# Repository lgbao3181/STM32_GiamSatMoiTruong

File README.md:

# Dự án STM32F103C8T6 – Giám sát nhiệt độ, độ ẩm và rò rỉ khí gas

## Giới thiệu

Đây là một dự án **Embedded Systems** sử dụng **STM32F103C8T6** làm vi điều khiển trung tâm để xây dựng hệ thống **giám sát nhiệt độ, độ ẩm và phát hiện rò rỉ khí gas**.

Firmware được phát triển bằng cách kết hợp **STM32CubeMX** để cấu hình phần cứng, ngoại vi và mã khởi tạo với **PlatformIO** để quản lý project, biên dịch và nạp firmware.

Hệ thống sử dụng:

* **AHT20** giao tiếp **I2C** để đo nhiệt độ và độ ẩm.
* **MQ-2** để phát hiện khí gas/khói và đưa tín hiệu cảnh báo về STM32.
* **LCD 16x2 giao tiếp I2C** để hiển thị nhiệt độ, độ ẩm và trạng thái cảnh báo.
* **Mạch chuyển mức logic 5V ↔ 3.3V** để bảo đảm tương thích mức điện áp giữa các thiết bị ngoại vi và STM32F103C8T6, đặc biệt trên các tín hiệu giao tiếp với LCD I2C và MQ-2.
* **Relay 5V** để điều khiển đèn cảnh báo **220V**.
* **UART** để truyền dữ liệu đo được từ STM32 lên PC.
* **Ứng dụng C# WinForms tự xây dựng** trên PC để hiển thị nhiệt độ, độ ẩm, trạng thái rò rỉ khí gas và đưa ra cảnh báo khi giá trị vượt ngưỡng cài đặt.

Mục tiêu của dự án là xây dựng một hệ thống giám sát thực tế, đồng thời thực hành các kỹ năng **STM32, I2C, GPIO, UART, điều khiển relay, xử lý ngưỡng cảnh báo và giao tiếp giữa MCU với phần mềm PC**.

---

## Video minh họa

https://github.com/user-attachments/assets/8e566ba1-eada-4bce-8f40-15832d237c19

---

## Sơ đồ nguyên lý

Sơ đồ nguyên lý thể hiện các khối chức năng chính của hệ thống:

* **STM32F103C8T6**: MCU trung tâm, thực hiện đọc cảm biến, xử lý điều kiện cảnh báo, điều khiển LCD, relay và truyền dữ liệu UART.
* **AHT20**: cảm biến nhiệt độ và độ ẩm, giao tiếp với STM32 thông qua I2C.
* **LCD 16x2 + module I2C**: hiển thị thông tin đo được và trạng thái cảnh báo.
* **MQ-2**: cảm biến dùng để phát hiện khí gas/khói; tín hiệu từ module được đưa qua mạch chuyển mức phù hợp trước khi vào MCU.
* **Mạch chuyển mức 5V ↔ 3.3V**: bảo đảm tương thích mức logic giữa STM32F103C8T6 và các ngoại vi sử dụng mức điện áp khác nhau, đặc biệt trên tuyến I2C của LCD và tín hiệu từ module MQ-2.
* **Relay 5V**: nhận tín hiệu điều khiển từ MCU để đóng/cắt đèn cảnh báo 220V.
* **USB–UART / UART**: cầu nối truyền dữ liệu giữa STM32 và PC.

## Thành phần phần cứng

| Thành phần | Số lượng | Vai trò |
| ------------------------------ | -------: | ----------------------------------------------- |
| STM32F103C8T6 | 1 | MCU trung tâm, xử lý dữ liệu và điều khiển hệ thống |
| AHT20 | 1 | Đo nhiệt độ và độ ẩm qua I2C |
| LCD 16x2 + module I2C | 1 | Hiển thị nhiệt độ, độ ẩm và cảnh báo |
| MQ-2 | 1 | Phát hiện khí gas/khói bằng ngõ ra số DO |
| Mạch chuyển mức 5V ↔ 3.3V | 1 | Tương thích mức logic giữa ngoại vi và STM32 |
| Relay 5V | 1 | Đóng/cắt tải cảnh báo |
| Đèn/tải 220V | 1 | Cảnh báo bằng tín hiệu đèn |
| USB–UART Converter | 1 | Cầu nối UART giữa STM32 và PC |
| PC / Laptop | 1 | Chạy ứng dụng WinForms để giám sát |

---

## Cấu hình giao tiếp và chân

> Một số chân GPIO phụ thuộc trực tiếp vào file cấu hình STM32CubeMX và project PlatformIO. Bảng dưới đây mô tả **chức năng giao tiếp**, còn số chân cụ thể nên lấy theo schematic/.ioc của phiên bản project đang sử dụng.

### AHT20 – STM32F103C8T6 (I2C)

| STM32 | Chức năng | AHT20 | Ghi chú |
| -------------------------------- | ------- | ----- | ------------------------------------------------ |
| **GPIO PB10** | I2C2 SCL | SCL | Đường xung clock của AHT20 |
| **GPIO PB11** | I2C2 SDA | SDA | Đường dữ liệu của AHT20 |
| 3.3V | Nguồn | VCC | Cấp nguồn theo thiết kế |
| GND | Mass | GND | **Bắt buộc nối chung** |

### LCD 16x2 – Module I2C – STM32

| STM32 / Bus | Chức năng | LCD I2C | Ghi chú |
| ---------------- | --------- | ------- | ------------------------------------------ |
| **GPIO PB6** | I2C1 SCL | SCL | Đường clock LCD, đi qua mạch chuyển mức |
| **GPIO PB7** | I2C1 SDA | SDA | Đường dữ liệu LCD, đi qua mạch chuyển mức |
| GND | Mass | GND | **Bắt buộc nối chung ở phía logic** |
| 5V | Nguồn LCD | VCC | Theo thiết kế phần cứng của module LCD |

### MQ-2 – STM32F103C8T6

| Tín hiệu | Chức năng | Kết nối MCU | Ghi chú |
| -------- | --------- | ----------- | ---------------------------------------------- |
| **DO** | Digital Output | **GPIO PA3** | Tín hiệu phải đi qua mạch chuyển mức 5V -> 3.3V trước khi vào MCU |
| VCC | Nguồn | 5V | Theo module MQ-2 |
| GND | Mass | GND | Nối chung với hệ thống |

> Trong project này, cảm biến MQ-2 được sử dụng thông qua ngõ ra số DO, không sử dụng ADC để đo hoặc tính toán nồng độ khí gas. Module MQ-2 được cấp nguồn 5V, do đó tín hiệu DO cần được đưa qua mạch chuyển mức logic/giảm áp trước khi kết nối với GPIO 3.3V của STM32F103C8T6.

> Về trạng thái tín hiệu, DO = 1 khi chưa phát hiện khí gas vượt ngưỡng cài đặt và DO = 0 khi phát hiện nồng độ khí vượt ngưỡng. Ngưỡng cảnh báo có thể được điều chỉnh bằng biến trở trên module MQ-2.

### Relay 5V – STM32F103C8T6

| Tín hiệu | Chức năng | MCU | Ghi chú |
| -------- | --------- | --- | -------------------------------------------- |
| **RELAY_CTRL** | Điều khiển relay | **GPIO PA4** | Firmware đặt mức HIGH khi có cảnh báo |
| VCC | Nguồn relay | 5V | Cấp nguồn theo module relay |
| GND | Mass | GND | Nối chung phía điều khiển |

Relay được sử dụng để đóng/cắt đèn cảnh báo **220V**.

> **Cảnh báo an toàn:** phần đèn cảnh báo 220V phải được cách ly và đấu nối đúng kỹ thuật. Không thao tác phần điện lưới khi đang cấp điện; ưu tiên sử dụng hộp bảo vệ, cầu chì/bảo vệ quá dòng và khoảng cách cách điện phù hợp.

### UART – STM32 ↔ PC

| STM32 | Chức năng | USB–UART Converter | Mục đích |
| -------- | ------- | ------------------ | -------------------------------- |
| GPIO PA9 | Transmit | RX | STM32 gửi dữ liệu lên PC |
| GPIO PA10 | Receive | TX | STM32 nhận dữ liệu từ PC nếu cần |
| GND | Mass | GND | **Bắt buộc nối chung** |

---

## Hệ thống giám sát và cảnh báo — phần trọng tâm của dự án

Mỗi chu kỳ hoạt động, firmware thực hiện việc đọc dữ liệu từ cảm biến, cập nhật LCD, kiểm tra các điều kiện cảnh báo, điều khiển relay/đèn và truyền dữ liệu lên PC.

### 1. Đọc nhiệt độ và độ ẩm từ AHT20

AHT20 giao tiếp với STM32F103C8T6 thông qua **I2C**.

Firmware khởi tạo AHT20 bằng `AHT20_Init()`, sau đó gọi `AHT20_Read(&temperature, &humidity)` để lấy nhiệt độ và độ ẩm. Hai giá trị này được dùng cho hiển thị LCD, xử lý cảnh báo và truyền UART.

Các giá trị này được sử dụng đồng thời cho **LCD tại thiết bị** và **ứng dụng WinForms trên PC**.

### 2. Phát hiện rò rỉ khí gas bằng MQ-2

MQ-2 được sử dụng ở **ngõ ra số DO** và firmware đọc trạng thái tại **GPIO PA3** bằng `HAL_GPIO_ReadPin()`. Project hiện tại dùng trạng thái số để cảnh báo, không tính nồng độ ppm bằng ADC.

Khi `PA3 == GPIO_PIN_RESET`, firmware xử lý đây là trạng thái cảnh báo gas:

* LCD hiển thị **`CANH BAO` / `RO RI KHI GA`**.
* GPIO **PA4** được đặt mức HIGH để kích **relay 5V** và đèn cảnh báo 220V.
* Trạng thái gas được truyền lên PC dưới trường `G` trong khung UART.
* Ứng dụng WinForms hiển thị trạng thái và cảnh báo tương ứng.

> Ngưỡng phát hiện thực tế của MQ-2 phụ thuộc module, mạch, thời gian làm nóng và cách hiệu chỉnh cảm biến. Vì vậy trạng thái **DO** trong project được xem là **tín hiệu cảnh báo theo cấu hình phần cứng**, không phải giá trị nồng độ ppm tuyệt đối.

### 3. Cảnh báo nhiệt độ vượt ngưỡng

Trong firmware hiện tại, hệ thống sử dụng hai ngưỡng môi trường:

* **Nhiệt độ > 35.0°C** → cảnh báo nhiệt độ cao.
* **Độ ẩm > 95.0%RH** → cảnh báo độ ẩm cao.

Khi một trong các điều kiện trên xảy ra, relay được kích hoạt và LCD chuyển sang màn hình cảnh báo tương ứng.

Ví dụ:

```text
Nhiệt độ / Độ ẩm vượt ngưỡng
              │
              ▼
       Kích hoạt cảnh báo
              │
        ┌─────┴─────┐
        ▼           ▼
   LCD cảnh báo   Relay / đèn
```

Firmware kiểm tra các điều kiện theo thứ tự **gas → nhiệt độ → độ ẩm**. Do đó, khi đồng thời có nhiều điều kiện cảnh báo, thông báo gas được ưu tiên hiển thị trước.

### 4. Hiển thị LCD 16x2

LCD được sử dụng để cung cấp thông tin trực tiếp tại thiết bị, giúp hệ thống có thể hoạt động mà không cần theo dõi PC liên tục.

Nội dung hiển thị được tổ chức theo các trạng thái. Khi hệ thống bình thường, firmware hiển thị:

```text
+----------------+
| NHIET DO: 28.50 C |
| DO AM: 65.20 %    |
+----------------+
```

Khi có sự cố, LCD chuyển sang thông báo cảnh báo:

```text
+----------------+
| CANH BAO      |
| RO RI KHI GA  |
+----------------+
```

### 5. Điều khiển relay và đèn cảnh báo 220V

STM32 xuất tín hiệu điều khiển tại **GPIO PA4** tới relay 5V. Trong firmware, PA4 được đặt **HIGH** khi có cảnh báo và **LOW** khi hệ thống bình thường.

Luồng điều khiển:

```text
Điều kiện cảnh báo
        │
        ▼
 STM32F103C8T6
        │
        ▼
 RELAY_CTRL(GPIO PA4)
        │
        ▼
   Relay 5V
        │
        ▼
   Đèn / tải 220V
```

Phần MCU chỉ xử lý tín hiệu điều khiển điện áp thấp; đèn cảnh báo 220V phải được bố trí và cách ly phù hợp với thiết kế phần cứng.

### 6. Truyền dữ liệu UART lên PC

STM32 truyền dữ liệu giám sát tới ứng dụng WinForms thông qua UART.

Firmware hiện tại tạo khung dữ liệu UART theo định dạng:

```text
@ T=%.2f H=%.2f G=%d &
```

Ví dụ:

```text
@ T=28.50 H=65.20 G=0 &
```

Trong đó:

* `T` — nhiệt độ hiện tại.
* `H` — độ ẩm hiện tại.
* `G` — trạng thái gas đọc từ GPIO PA3 (`0` hoặc `1`).

Khung dữ liệu được gửi sau mỗi chu kỳ **1 giây**.

---

## Ứng dụng WinForms trên PC

Ứng dụng **C# WinForms** được tự xây dựng để làm giao diện giám sát phía PC.

Các chức năng chính:

* Kết nối tới cổng COM của STM32 thông qua USB–UART.
* Nhận dữ liệu UART theo thời gian thực.
* Hiển thị **nhiệt độ** và **độ ẩm**.
* Hiển thị trạng thái **rò rỉ khí gas**.
* Hiển thị trạng thái **cảnh báo**.
* Cảnh báo khi nhiệt độ vượt **35°C**.
* Cảnh báo khi độ ẩm vượt **95%RH**.
* Cảnh báo khi MQ-2 báo trạng thái gas.

Kiến trúc giao tiếp tổng quát:

```text
┌─────────────────────────┐
│      STM32F103C8T6      │
│                         │
│ AHT20 ── I2C2 ─┐        │
│ MQ-2 ── GPIO ──┤        │
│                │        │
│ LCD ── I2C1 ───┤        │
│ Relay ─ GPIO ──┤        │
│                │        │
│        UART ───┴────────┼────────┐
└─────────────────────────┘        │
                                   ▼
                        ┌──────────────────────┐
                        │      USB–UART        │
                        └──────────┬───────────┘
                                   │
                                   ▼
                        ┌──────────────────────┐
                        │    C# WinForms       │
                        │                      │
                        │ - Nhiệt độ           │
                        │ - Độ ẩm              │
                        │ - Rò rỉ khí gas      │
                        │ - Cảnh báo            │
                        └──────────────────────┘
```

---

## Kiến trúc hệ thống tổng quan

```text
                           ┌──────────────────────┐
                           │      PC / Laptop     │
                           │     C# WinForms      │
                           └──────────┬───────────┘
                                      │
                                      │ UART
                                      ▼
┌─────────────────────────────────────────────────────────┐
│                   STM32F103C8T6                         │
│                                                         │
│  ┌─────────────┐       ┌────────────────────────────┐  │
│  │    AHT20    │◄──I2C─┤ Đọc nhiệt độ + độ ẩm      │  │
│  └─────────────┘       └──────────────┬─────────────┘  │
│                                       │                │
│  ┌─────────────┐                      ▼                │
│  │    MQ-2     │──GPIO──►     Xử lý ngưỡng cảnh báo   │
│  └─────────────┘                      │                │
│                                       ├────► LCD 16x2 │
│  ┌─────────────┐                      │       (I2C)   │
│  │ Mạch chuyển │◄──── 5V ↔ 3.3V ────┤                │
│  │ mức logic   │                      ├────► Relay 5V │
│  └─────────────┘                      │                │
│                                       └────► UART ─────┼──► PC
└─────────────────────────────────────────────────────────┘
                                                  │
                                                  ▼
                                         ┌────────────────┐
                                         │  Đèn / tải     │
                                         │      220V      │
                                         └────────────────┘
```

### Quy trình hoạt động

1. **Khởi tạo:** STM32F103C8T6 khởi tạo GPIO, I2C1, I2C2 và USART1; sau đó gọi `AHT20_Init()` và `LCD_I2C_Init()`.
2. **Đọc cảm biến:** STM32 đọc nhiệt độ/độ ẩm từ AHT20 và đọc trạng thái số của MQ-2 tại **PA3**.
3. **Xử lý cảnh báo:** firmware kiểm tra theo thứ tự **gas → nhiệt độ > 35°C → độ ẩm > 95%RH**.
4. **Hiển thị tại thiết bị:** LCD 16x2 hiển thị thông báo cảnh báo hoặc nhiệt độ, độ ẩm khi hệ thống bình thường.
5. **Điều khiển cảnh báo:** GPIO **PA4** được đặt HIGH khi có cảnh báo để kích relay 5V; khi bình thường PA4 được đặt LOW.
6. **Truyền dữ liệu:** USART1 gửi khung `@ T=... H=... G=... &` lên PC.
7. **Chu kỳ:** sau mỗi vòng xử lý, firmware chờ `HAL_Delay(1000)` trước lần đọc tiếp theo.

---

## Bắt đầu

### Yêu cầu phần mềm

| Phần mềm | Phiên bản | Mục đích |
| -------------------------------- | --------- | ----------------------------------------------- |
| STM32CubeMX | Theo phiên bản project | Cấu hình MCU, GPIO, I2C1, I2C2, USART1 và sinh mã khởi tạo |
| PlatformIO | Mới nhất | Quản lý project, biên dịch và nạp firmware |
| VS Code | Khuyến nghị | Môi trường phát triển cho PlatformIO |
| STM32Cube HAL | Theo project | Thư viện HAL sử dụng trong firmware |
| C# / .NET WinForms | Theo project | Phát triển ứng dụng giám sát trên PC |
| ST-LINK Utility / STM32CubeProgrammer | Theo môi trường sử dụng | Nạp và kiểm tra firmware |
| Serial Terminal | Bất kỳ | Kiểm thử UART và debug |

### Lắp phần cứng

* Kết nối **AHT20** với bus I2C của STM32.
* Kết nối **LCD 16x2 I2C** qua mạch chuyển mức logic nếu module hoạt động ở 5V.
* Kết nối **MQ-2** theo thiết kế; nếu tín hiệu đưa vào MCU là tín hiệu 5V thì phải chuyển mức/giảm áp về mức phù hợp với STM32.
* Kết nối **Relay 5V** với chân điều khiển của MCU thông qua mạch driver phù hợp với tải của relay.
* Kết nối tải/đèn **220V** vào tiếp điểm relay theo đúng thiết kế điện và yêu cầu an toàn.
* Kết nối **UART của STM32** với USB–UART Converter để giao tiếp với PC.
* Nối chung GND ở phía mạch logic theo thiết kế.

### Cài đặt

1. Sao chép repository:

```bash
git clone <repository-url>
cd <repository-folder>
```

2. Mở thư mục project bằng **Visual Studio Code + PlatformIO**.

3. Kiểm tra cấu hình trong `platformio.ini` và bảo đảm board STM32F103C8T6 đúng với project.

4. Đối chiếu cấu hình GPIO/I2C/UART với file cấu hình **STM32CubeMX** và schematic.

5. Biên dịch firmware:

```bash
pio run
```

6. Nạp firmware bằng ST-LINK hoặc phương thức upload được cấu hình trong `platformio.ini`:

```bash
pio run -t upload
```

7. Kết nối USB–UART với PC và xác định đúng cổng COM.

8. Mở ứng dụng WinForms.

9. Khởi động hệ thống và kiểm tra dữ liệu nhiệt độ, độ ẩm, trạng thái MQ-2 và cảnh báo.

### Kiểm thử hệ thống

Các nội dung cần kiểm tra:

* STM32F103C8T6 khởi động bình thường.
* AHT20 trả về dữ liệu nhiệt độ và độ ẩm hợp lệ.
* LCD 16x2 hiển thị đúng nội dung.
* Mạch chuyển mức 5V ↔ 3.3V hoạt động ổn định trên các đường tín hiệu cần thiết.
* MQ-2 thay đổi trạng thái khi xuất hiện điều kiện phát hiện khí theo cấu hình module.
* Relay 5V đóng/cắt đúng theo tín hiệu điều khiển.
* Đèn/tải 220V hoạt động đúng theo relay.
* UART truyền dữ liệu ổn định lên PC.
* WinForms nhận và hiển thị dữ liệu đúng.
* Cảnh báo xuất hiện khi **temperature > 35.0°C**.
* Cảnh báo xuất hiện khi **humidity > 95.0%RH**.
* Cảnh báo xuất hiện khi **MQ-2 DO = HIGH**.

---

## Cấu trúc project đề xuất

```text
.
├── firmware/
│   ├── include/
│   ├── lib/
│   ├── src/
│   ├── test/
│   └── platformio.ini
│
├── cube_mx/
│   └── *.ioc
│
├── pc_app/
│   └── WinForms project
│
├── demo/
│   ├── Schematic.svg
│   ├── PCB.svg
│   └── ...
│
└── README.md
```

> Cấu trúc trên mang tính mô tả; tên thư mục thực tế cần giữ đúng theo repository hiện tại của dự án.

---

## Tài liệu tham khảo

* [Datasheet STM32F103C8](https://www.st.com/resource/en/datasheet/stm32f103c8.pdf)
* [STM32CubeMX](https://www.st.com/en/development-tools/stm32cubemx.html)
* [PlatformIO Documentation](https://docs.platformio.org/)
* [AHT20 Datasheet](https://www.aosong.com/userfiles/files/media/AHT20%20datasheet%20Version-1.0.pdf)
* [Microsoft .NET](https://learn.microsoft.com/en-us/dotnet/)
* [Windows Forms](https://learn.microsoft.com/en-us/dotnet/desktop/winforms/)

---

## Trạng thái dự án

* **Trạng thái:** Hoàn thành
* **Phiên bản:** v1.0
* **Cập nhật lần cuối:** Tháng 9/2026

---

## Liên hệ

**Gia Bảo**

📧 Email: *[your-email@example.com](mailto:your-email@example.com)*  
🐙 GitHub: *your-github-profile*

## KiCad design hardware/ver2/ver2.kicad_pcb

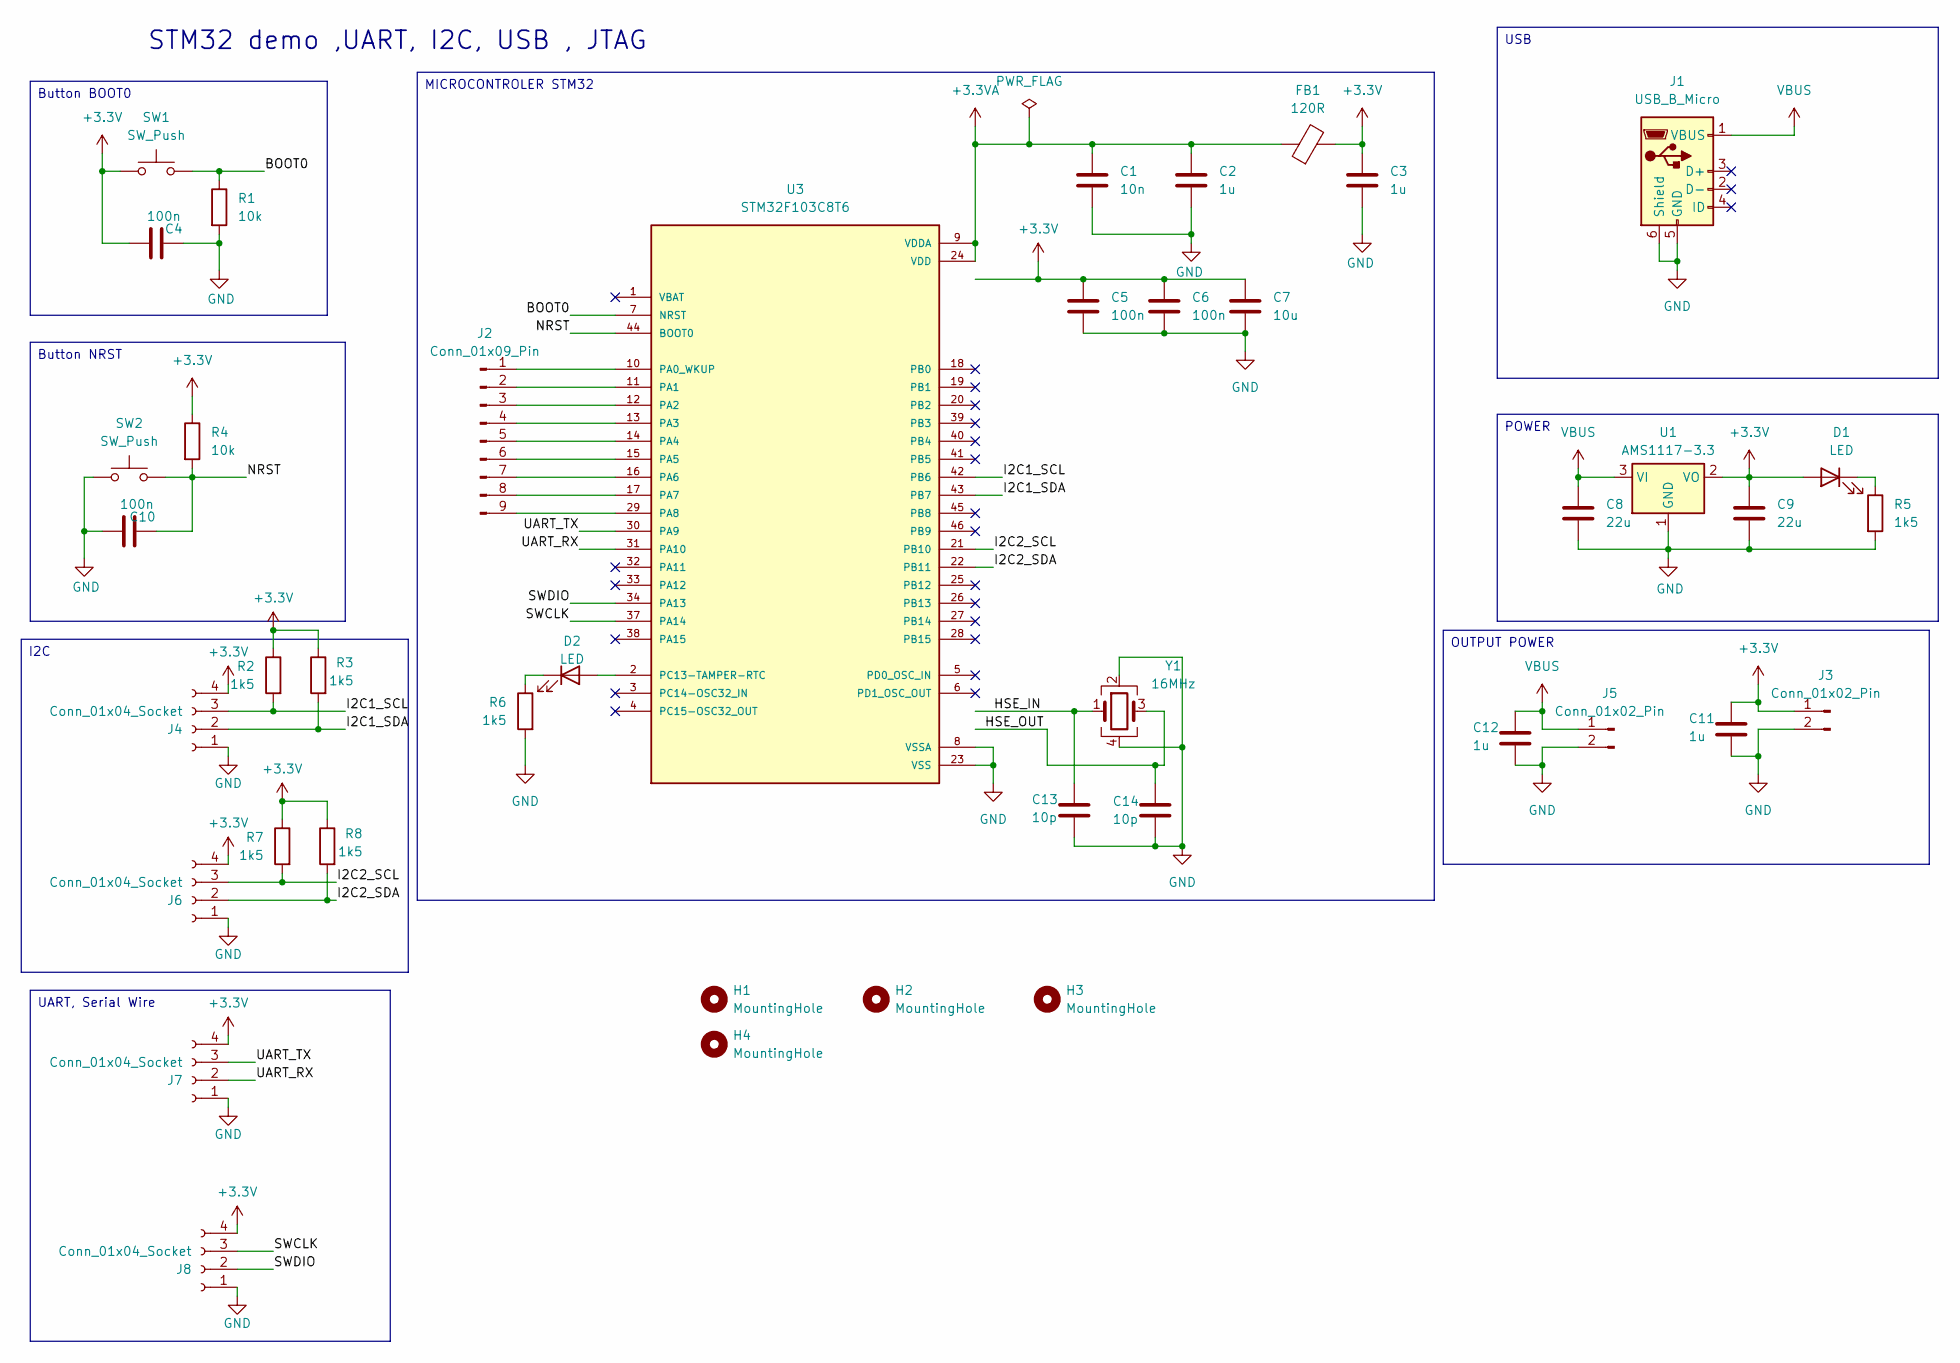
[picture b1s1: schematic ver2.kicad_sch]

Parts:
C1: 10n; C_0805_2012Metric
C2, C3, C11, C12: 1u; C_0805_2012Metric
C4, C5, C6, C10: 100n; C_0805_2012Metric
C7: 10u; C_0805_2012Metric
C8, C9: 22u; C_0805_2012Metric
C13, C14: 10p; C_0805_2012Metric
D1, D2: LED; LED_0805_2012Metric
FB1: 120R; L_0805_2012Metric
H1, H2, H3, H4: MountingHole; MountingHole_2.2mm_M2
J1: USB_B_Micro; USB_Micro-B_Wuerth_629105150521
J2: Conn_01x09_Pin; PinHeader_1x09_P2.54mm_Vertical
J3, J5: Conn_01x02_Pin; PinHeader_1x02_P2.54mm_Vertical
J4, J6, J7, J8: Conn_01x04_Socket; PinHeader_1x04_P2.54mm_Vertical
R1, R4: 10k; R_0805_2012Metric
R2, R3, R5, R6, R7, R8: 1k5; R_0805_2012Metric
SW1, SW2: SW_Push; SW_Push_1P1T_NO_E-Switch_TL3301NxxxxxG
U1: AMS1117-3.3; SOT-223-3_TabPin2
U3: STM32F103C8T6; QFP50P900X900X160-48N; PARTREV 10
Y1: 16MHz; Crystal_SMD_3225-4Pin_3.2x2.5mm

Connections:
+3.3V: C3.1, C4.1, C5.1, C6.1, C7.1, C9.1, C11.1, D1.2 (A), FB1.2, J3.1, J4.4, J6.4, J7.4, J8.4, R2.1, R3.1, R4.1, R7.1, R8.1, SW1.1, U1.2 (VO)
+3.3VA: C1.1, C2.1, FB1.1, U3.9 (VDDA), U3.24 (VDD), U3.36 (VDD), U3.48 (VDD)
/BOOT0: R1.1, SW1.2, U3.7 (NRST)
/HSE_IN: C13.1, Y1.1
/HSE_OUT: C14.1, Y1.3
/I2C1_SCL: J4.3, R2.2, U3.42 (PB6)
/I2C1_SDA: J4.2, R3.2, U3.43 (PB7)
/I2C2_SCL: J6.3, R7.2, U3.21 (PB10)
/I2C2_SDA: J6.2, R8.2, U3.22 (PB11)
/NRST: C10.2, R4.2, SW2.2, U3.44 (BOOT0)
/SWCLK: J8.3, U3.37 (PA14)
/SWDIO: J8.2, U3.34 (PA13)
/UART_RX: J7.2, U3.31 (PA10)
/UART_TX: J7.3, U3.30 (PA9)
GND: C1.2, C2.2, C3.2, C4.2, C5.2, C6.2, C7.2, C8.2, C9.2, C10.1, C11.2, C12.2, C13.2, C14.2, J1.5 (GND), J1.6 (Shield), J3.2, J4.1, J5.2, J6.1, J7.1, J8.1, R1.2, R5.2, R6.2, SW2.1, U1.1 (GND), U3.8 (VSSA), U3.23 (VSS), U3.35 (VSS), U3.47 (VSS), Y1.2, Y1.4
unnamed: D1.1 (K), R5.1
unnamed: D2.2 (A), U3.2 (PC13-TAMPER-RTC)
unnamed: D2.1 (K), R6.1
unnamed: J2.1, U3.10 (PA0_WKUP)
unnamed: J2.2, U3.11 (PA1)
unnamed: J2.3, U3.12 (PA2)
unnamed: J2.4, U3.13 (PA3)
unnamed: J2.5, U3.14 (PA4)
unnamed: J2.6, U3.15 (PA5)
unnamed: J2.7, U3.16 (PA6)
unnamed: J2.8, U3.17 (PA7)
unnamed: J2.9, U3.29 (PA8)
VBUS: C8.1, C12.1, J1.1 (VBUS), J5.1, U1.3 (VI)

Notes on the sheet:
STM32 demo ,UART, I2C, USB , JTAG
POWER
UART, Serial Wire
OUTPUT POWER
Button BOOT0
MICROCONTROLER STM32
USB
Button NRST
I2C

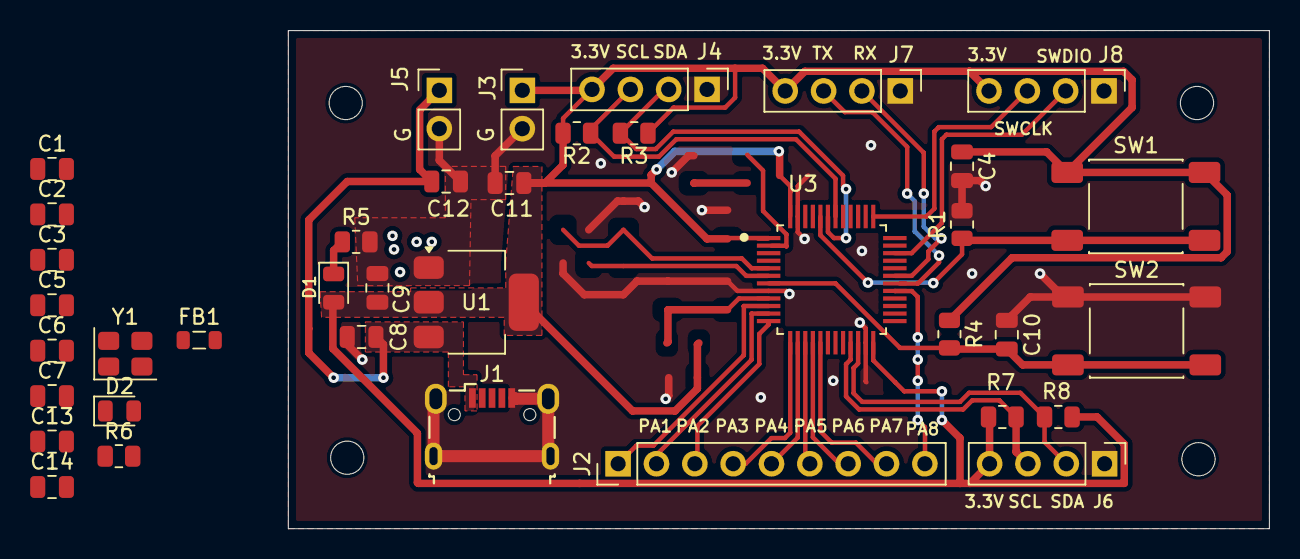
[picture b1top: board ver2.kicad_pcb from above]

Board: 2 copper layers, 65.0 x 33.0 mm, 42 parts (0 on the bottom side), 28 nets.

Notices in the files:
README.md:
License: MIT
